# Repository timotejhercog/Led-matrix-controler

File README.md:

🚀 Led matrix controler

This project is currently under active development. More features, files, and updates are on the way!

📖 About The Project

Welcome to the repository! This project is still early in development, things are constantly changing, improving, and expanding.

✨ What's Here So Far

PCB files

MIDEM paper

📫 Stay Tuned

Thank you for checking out the project! Feel free to star ⭐ the repository to follow along with future updates.

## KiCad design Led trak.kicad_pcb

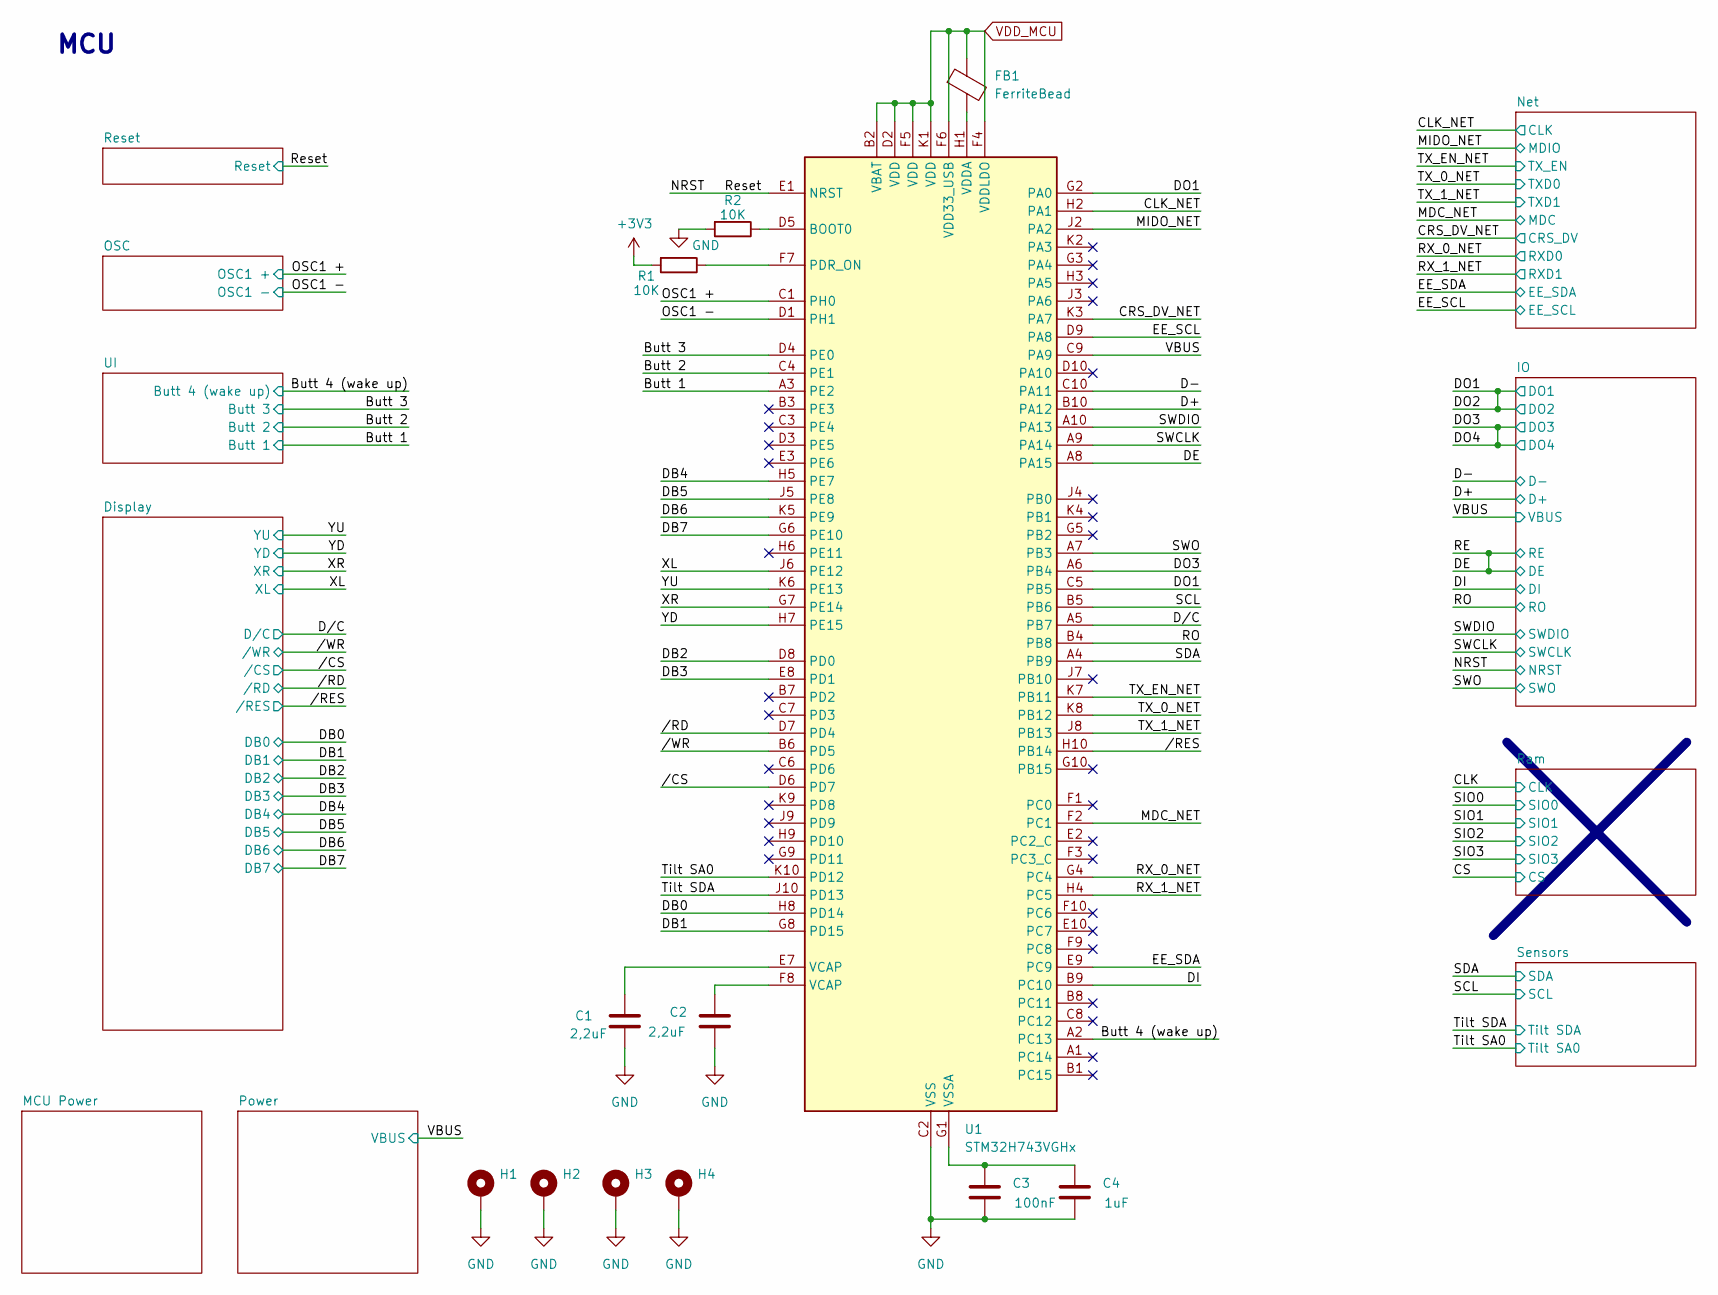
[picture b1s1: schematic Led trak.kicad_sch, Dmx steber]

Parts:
C1, C2: 2,2uF; C_0603_1608Metric
C3: 100nF; C_0603_1608Metric
C4: 1uF; C_0603_1608Metric
FB1: FerriteBead; C_0201_0603Metric
H1, H2, H3, H4: MountingHole_Pad_MP; MountingHole_3.2mm_M3_Pad_Via
R1, R2: 10K; C_0402_1005Metric
U1: STM32H743VGHx; TFBGA-100_8x8mm_Layout10x10_P0.8mm

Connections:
/Butt 1: U1.A3 (PE2); also elsewhere on the board
/Butt 2: U1.C4 (PE1); also elsewhere on the board
/Butt 3: U1.D4 (PE0); also elsewhere on the board
/Butt 4 (wake up): U1.A2 (PC13); also elsewhere on the board
/CLK_NET: U1.H2 (PA1); also elsewhere on the board
/CRS_DV_NET: U1.K3 (PA7); also elsewhere on the board
/D+: U1.B10 (PA12); also elsewhere on the board
/D-: U1.C10 (PA11); also elsewhere on the board
/DB0: U1.H8 (PD14); also elsewhere on the board
/DB1: U1.G8 (PD15); also elsewhere on the board
/DB2: U1.D8 (PD0); also elsewhere on the board
/DB3: U1.E8 (PD1); also elsewhere on the board
/DB4: U1.H5 (PE7); also elsewhere on the board
/DB5: U1.J5 (PE8); also elsewhere on the board
/DB6: U1.K5 (PE9); also elsewhere on the board
/DB7: U1.G6 (PE10); also elsewhere on the board
/DE: U1.A8 (PA15); also elsewhere on the board
/DI: U1.B9 (PC10); also elsewhere on the board
/DO1: U1.C5 (PB5), U1.G2 (PA0); also elsewhere on the board
/DO3: U1.A6 (PB4); also elsewhere on the board
/D/C: U1.A5 (PB7); also elsewhere on the board
/EE_SCL: U1.D9 (PA8); also elsewhere on the board
/EE_SDA: U1.E9 (PC9); also elsewhere on the board
/MDC_NET: U1.F2 (PC1); also elsewhere on the board
/MIDO_NET: U1.J2 (PA2); also elsewhere on the board
/NRST: U1.E1 (NRST); also elsewhere on the board
/OSC1 +: U1.C1 (PH0); also elsewhere on the board
/OSC1 -: U1.D1 (PH1); also elsewhere on the board
/RO: U1.B4 (PB8); also elsewhere on the board
/RX_0_NET: U1.G4 (PC4); also elsewhere on the board
/RX_1_NET: U1.H4 (PC5); also elsewhere on the board
/SCL: U1.B5 (PB6); also elsewhere on the board
/SDA: U1.A4 (PB9); also elsewhere on the board
/SWCLK: U1.A9 (PA14); also elsewhere on the board
/SWDIO: U1.A10 (PA13); also elsewhere on the board
/SWO: U1.A7 (PB3); also elsewhere on the board
/TX_0_NET: U1.K8 (PB12); also elsewhere on the board
/TX_1_NET: U1.J8 (PB13); also elsewhere on the board
/TX_EN_NET: U1.K7 (PB11); also elsewhere on the board
/Tilt SA0: U1.K10 (PD12); also elsewhere on the board
/Tilt SDA: U1.J10 (PD13); also elsewhere on the board
/VBUS: U1.C9 (PA9); also elsewhere on the board
/XL: U1.J6 (PE12); also elsewhere on the board
/XR: U1.G7 (PE14); also elsewhere on the board
/YD: U1.H7 (PE15); also elsewhere on the board
/YU: U1.K6 (PE13); also elsewhere on the board
//CS: U1.D6 (PD7); also elsewhere on the board
//RD: U1.D7 (PD4); also elsewhere on the board
//RES: U1.H10 (PB14); also elsewhere on the board
//WR: U1.B6 (PD5); also elsewhere on the board
GND: C1.2, C2.2, C3.2, C4.2, H1.MP, H2.MP, H3.MP, H4.MP, R2.2, U1.C2 (VSS), U1.E4 (VSS), U1.E5 (VSS), U1.E6 (VSS), U1.J1 (VSS); also elsewhere on the board
unnamed: C1.1, U1.E7 (VCAP)
unnamed: C2.1, U1.F8 (VCAP)
unnamed: R2.1, U1.D5 (BOOT0)
unnamed: R1.1, U1.F7 (PDR_ON)
unnamed: FB1.2, U1.H1 (VDDA)
unnamed: C3.1, C4.1, U1.G1 (VSSA)
VDD_MCU: FB1.1, R1.2, U1.B2 (VBAT), U1.D2 (VDD), U1.F4 (VDDLDO), U1.F5 (VDD), U1.F6 (VDD33_USB), U1.K1 (VDD); also elsewhere on the board

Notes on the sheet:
MCU

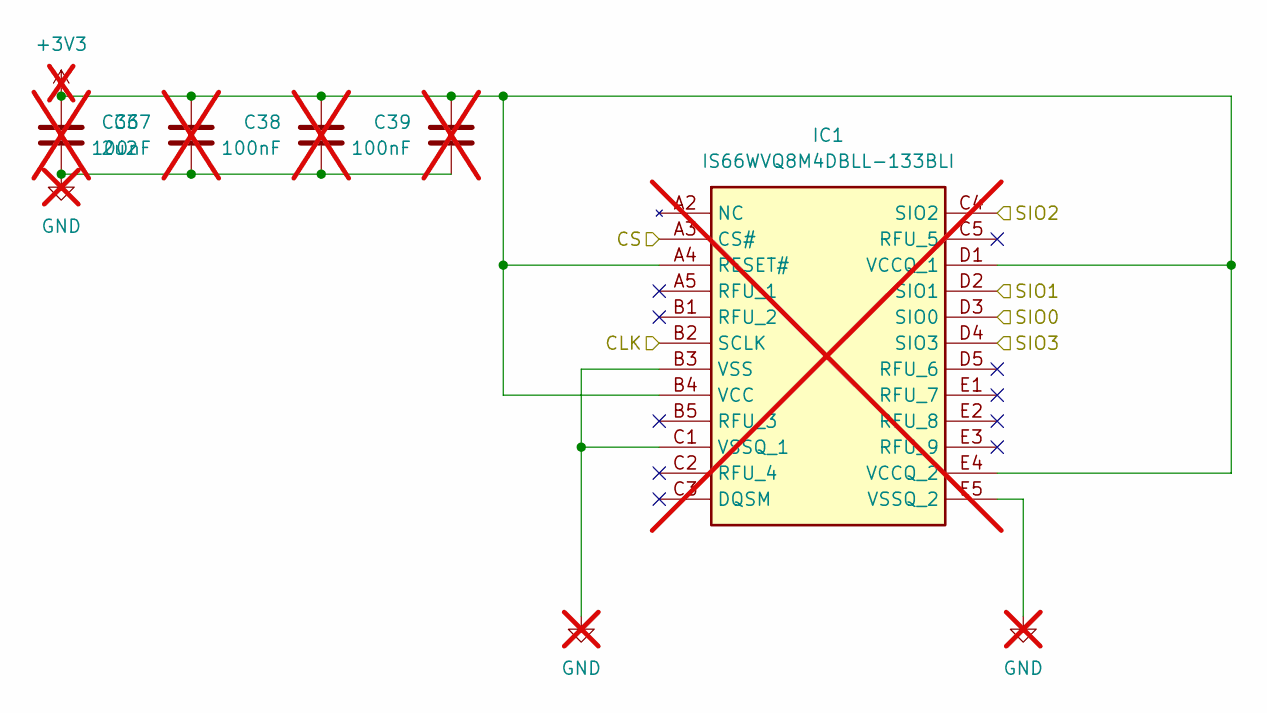
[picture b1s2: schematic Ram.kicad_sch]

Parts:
C36: 2u2; C_0603_1608Metric; not fitted
C37, C38, C39: 100nF; C_0402_1005Metric; not fitted
IC1: IS66WVQ8M4DBLL-133BLI; BGA24C100P5X5_600X800X120; Manufacturer_Part_Number IS66WVQ8M4DBLL-133BLI; Mouser Part Number 870-ISQ8M4DBLL133BLI; not fitted

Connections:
unnamed: C36.1, C37.1, C38.1, C39.1, IC1.A4 (RESET#), IC1.B4 (VCC), IC1.D1 (VCCQ_1), IC1.E4 (VCCQ_2)
unnamed: C36.2, C37.2, C38.2, C39.2, IC1.B3 (VSS), IC1.C1 (VSSQ_1), IC1.E5 (VSSQ_2)

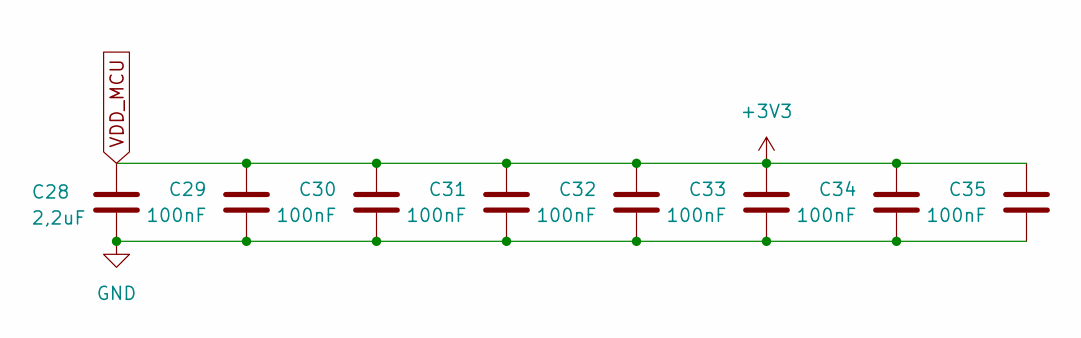
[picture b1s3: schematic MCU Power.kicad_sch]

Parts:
C28: 2,2uF; C_0603_1608Metric
C29, C30, C31, C32, C33, C34, C35: 100nF; C_0402_1005Metric

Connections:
GND: C28.2, C29.2, C30.2, C31.2, C32.2, C33.2, C34.2, C35.2; also elsewhere on the board
VDD_MCU: C28.1, C29.1, C30.1, C31.1, C32.1, C33.1, C34.1, C35.1; also elsewhere on the board

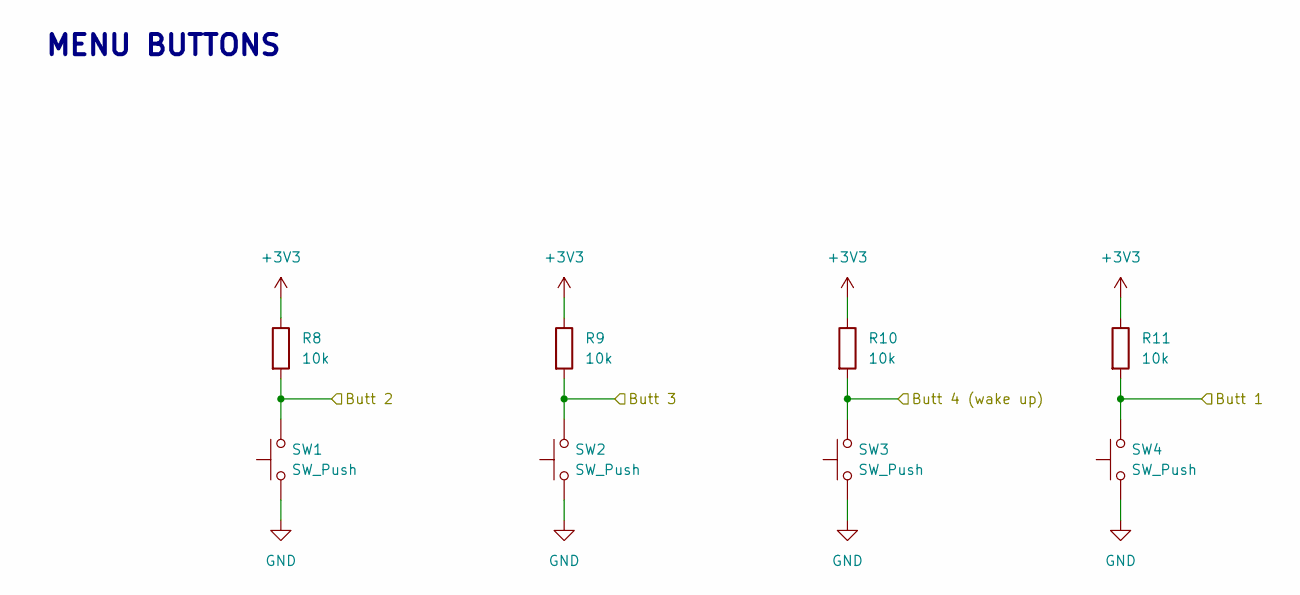
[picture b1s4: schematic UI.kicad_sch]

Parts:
R8, R9, R10, R11: 10k; C_0402_1005Metric
SW1, SW2, SW3, SW4: SW_Push; SW_Push_1TS009xxxx-xxxx-xxxx_6x6x5mm

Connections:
/Butt 1: R11.2, SW4.2; also elsewhere on the board
/Butt 2: R8.2, SW1.2; also elsewhere on the board
/Butt 3: R9.2, SW2.2; also elsewhere on the board
/Butt 4 (wake up): R10.2, SW3.2; also elsewhere on the board
GND: SW1.1, SW2.1, SW3.1, SW4.1; also elsewhere on the board
VDD_MCU: R8.1, R9.1, R10.1, R11.1; also elsewhere on the board

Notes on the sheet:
MENU BUTTONS

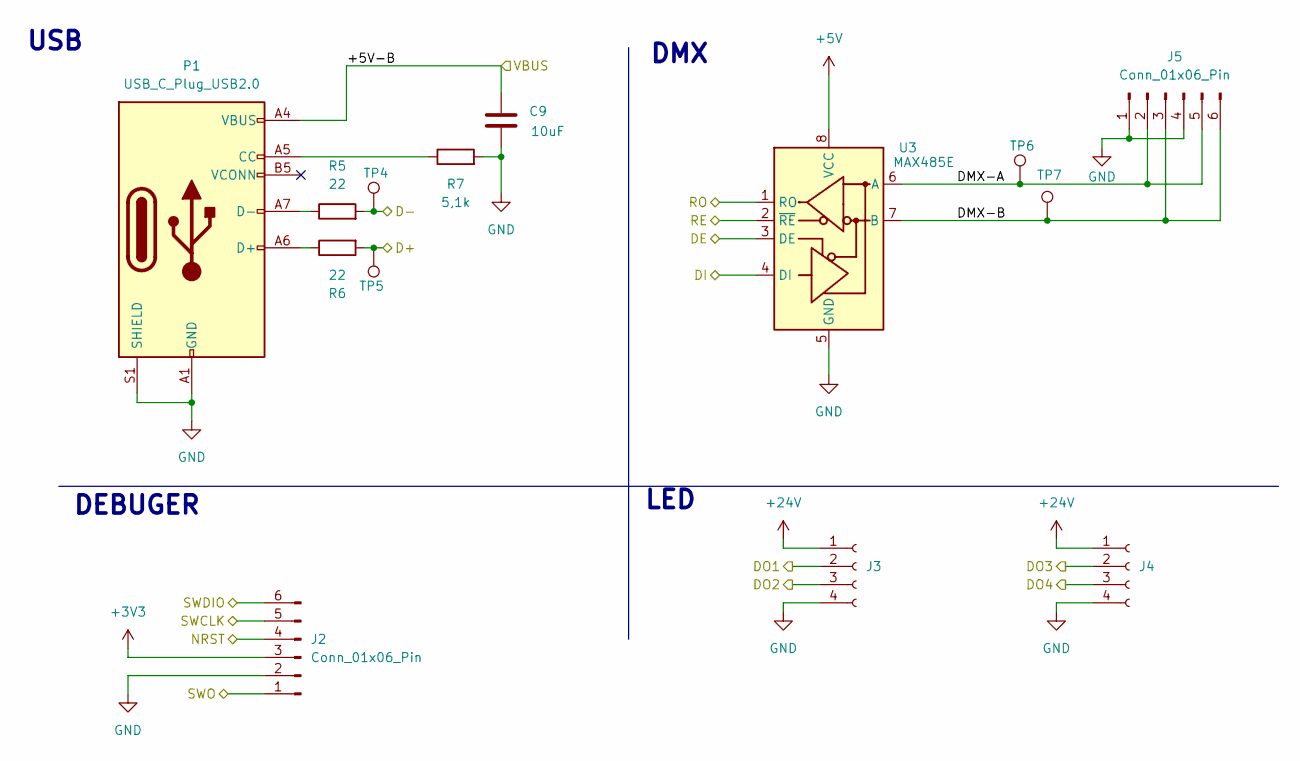
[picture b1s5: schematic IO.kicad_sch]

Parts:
C9: 10uF; C_0603_1608Metric
J2: Conn_01x06_Pin; PinSocket_1x06_P2.54mm_Vertical
J3, J4: Conn_01x04_Socket; Molex_PicoBlade_53047-0410_1x04_P1.25mm_Vertical
J5: Conn_01x06_Pin; Molex_PicoBlade_53047-0610_1x06_P1.25mm_Vertical
P1: USB_C_Plug_USB2.0; USB_C_Receptacle_HRO_TYPE-C-31-M-12
R5, R6: 22; C_0402_1005Metric
R7: 5,1k; C_0402_1005Metric
TP4, TP5, TP6, TP7: TestPoint; TestPoint_Pad_D1.5mm
U3: MAX485E; SOIC-8_3.9x4.9mm_P1.27mm

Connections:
+5V: U3.8 (VCC); also elsewhere on the board
+24V: J3.1, J4.1; also elsewhere on the board
/D+: R6.2, TP5.1; also elsewhere on the board
/D-: R5.2, TP4.1; also elsewhere on the board
/DE: U3.2 (~RE), U3.3 (DE); also elsewhere on the board
/DI: U3.4 (DI); also elsewhere on the board
/DO1: J3.2, J3.3; also elsewhere on the board
/DO3: J4.2, J4.3; also elsewhere on the board
/IO/DMX-A: J5.2, J5.5, TP6.1, U3.6 (A)
/IO/DMX-B: J5.3, J5.6, TP7.1, U3.7 (B)
/NRST: J2.4; also elsewhere on the board
/RO: U3.1 (RO); also elsewhere on the board
/SWCLK: J2.5; also elsewhere on the board
/SWDIO: J2.6; also elsewhere on the board
/SWO: J2.1; also elsewhere on the board
/VBUS: C9.1, P1.A4 (VBUS), P1.A9 (VBUS), P1.B4 (VBUS), P1.B9 (VBUS); also elsewhere on the board
GND: C9.2, J2.2, J3.4, J4.4, J5.1, J5.4, P1.A1 (GND), P1.A12 (GND), P1.B1 (GND), P1.B12 (GND), P1.S1 (SHIELD), R7.2, U3.5 (GND); also elsewhere on the board
unnamed: P1.A5 (CC), R7.1
unnamed: P1.A6 (D+), R6.1
unnamed: P1.A7 (D-), R5.1
VDD_MCU: J2.3; also elsewhere on the board

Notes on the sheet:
LED
DEBUGER
DMX
USB

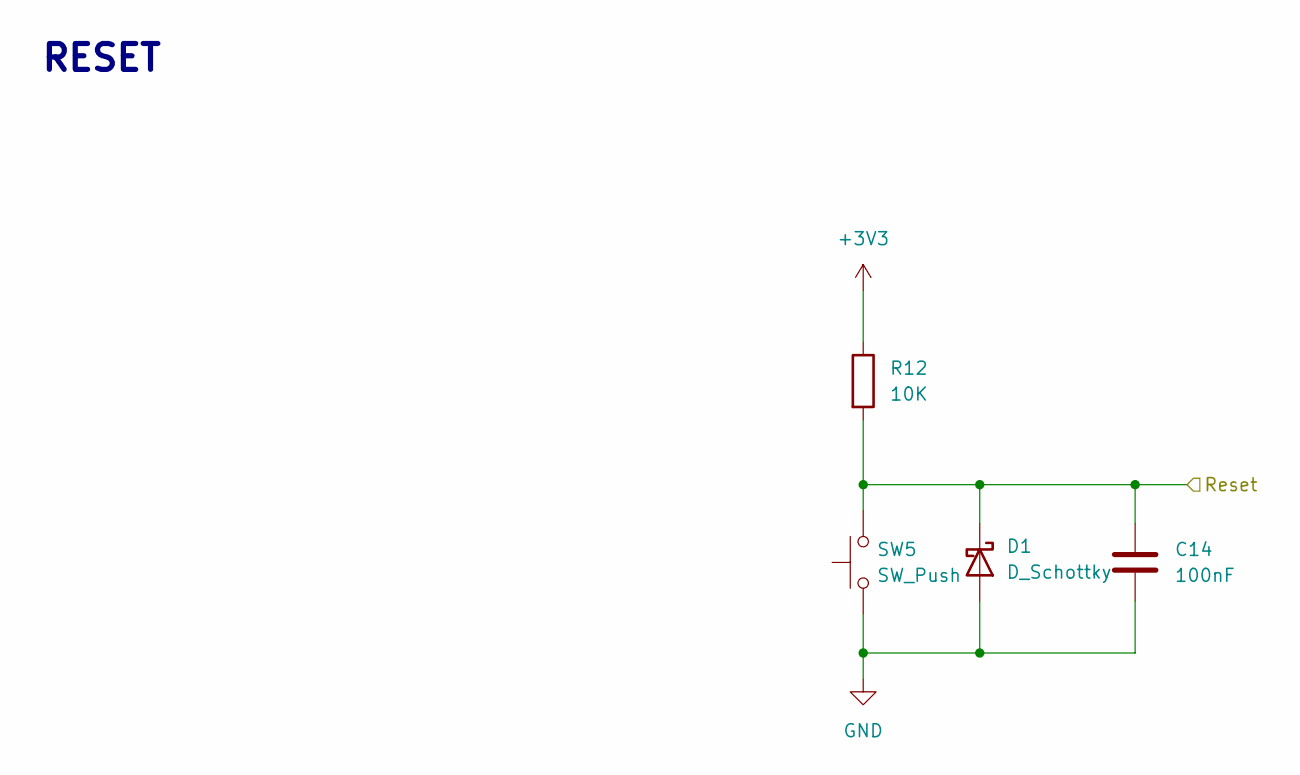
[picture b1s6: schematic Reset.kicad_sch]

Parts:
C14: 100nF; C_0402_1005Metric
D1: D_Schottky; D_SMA
R12: 10K; C_0402_1005Metric
SW5: SW_Push; SW_Push_1TS009xxxx-xxxx-xxxx_6x6x5mm

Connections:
/NRST: C14.1, D1.1 (K), R12.2, SW5.2; also elsewhere on the board
GND: C14.2, D1.2 (A), SW5.1; also elsewhere on the board
VDD_MCU: R12.1; also elsewhere on the board

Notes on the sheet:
RESET

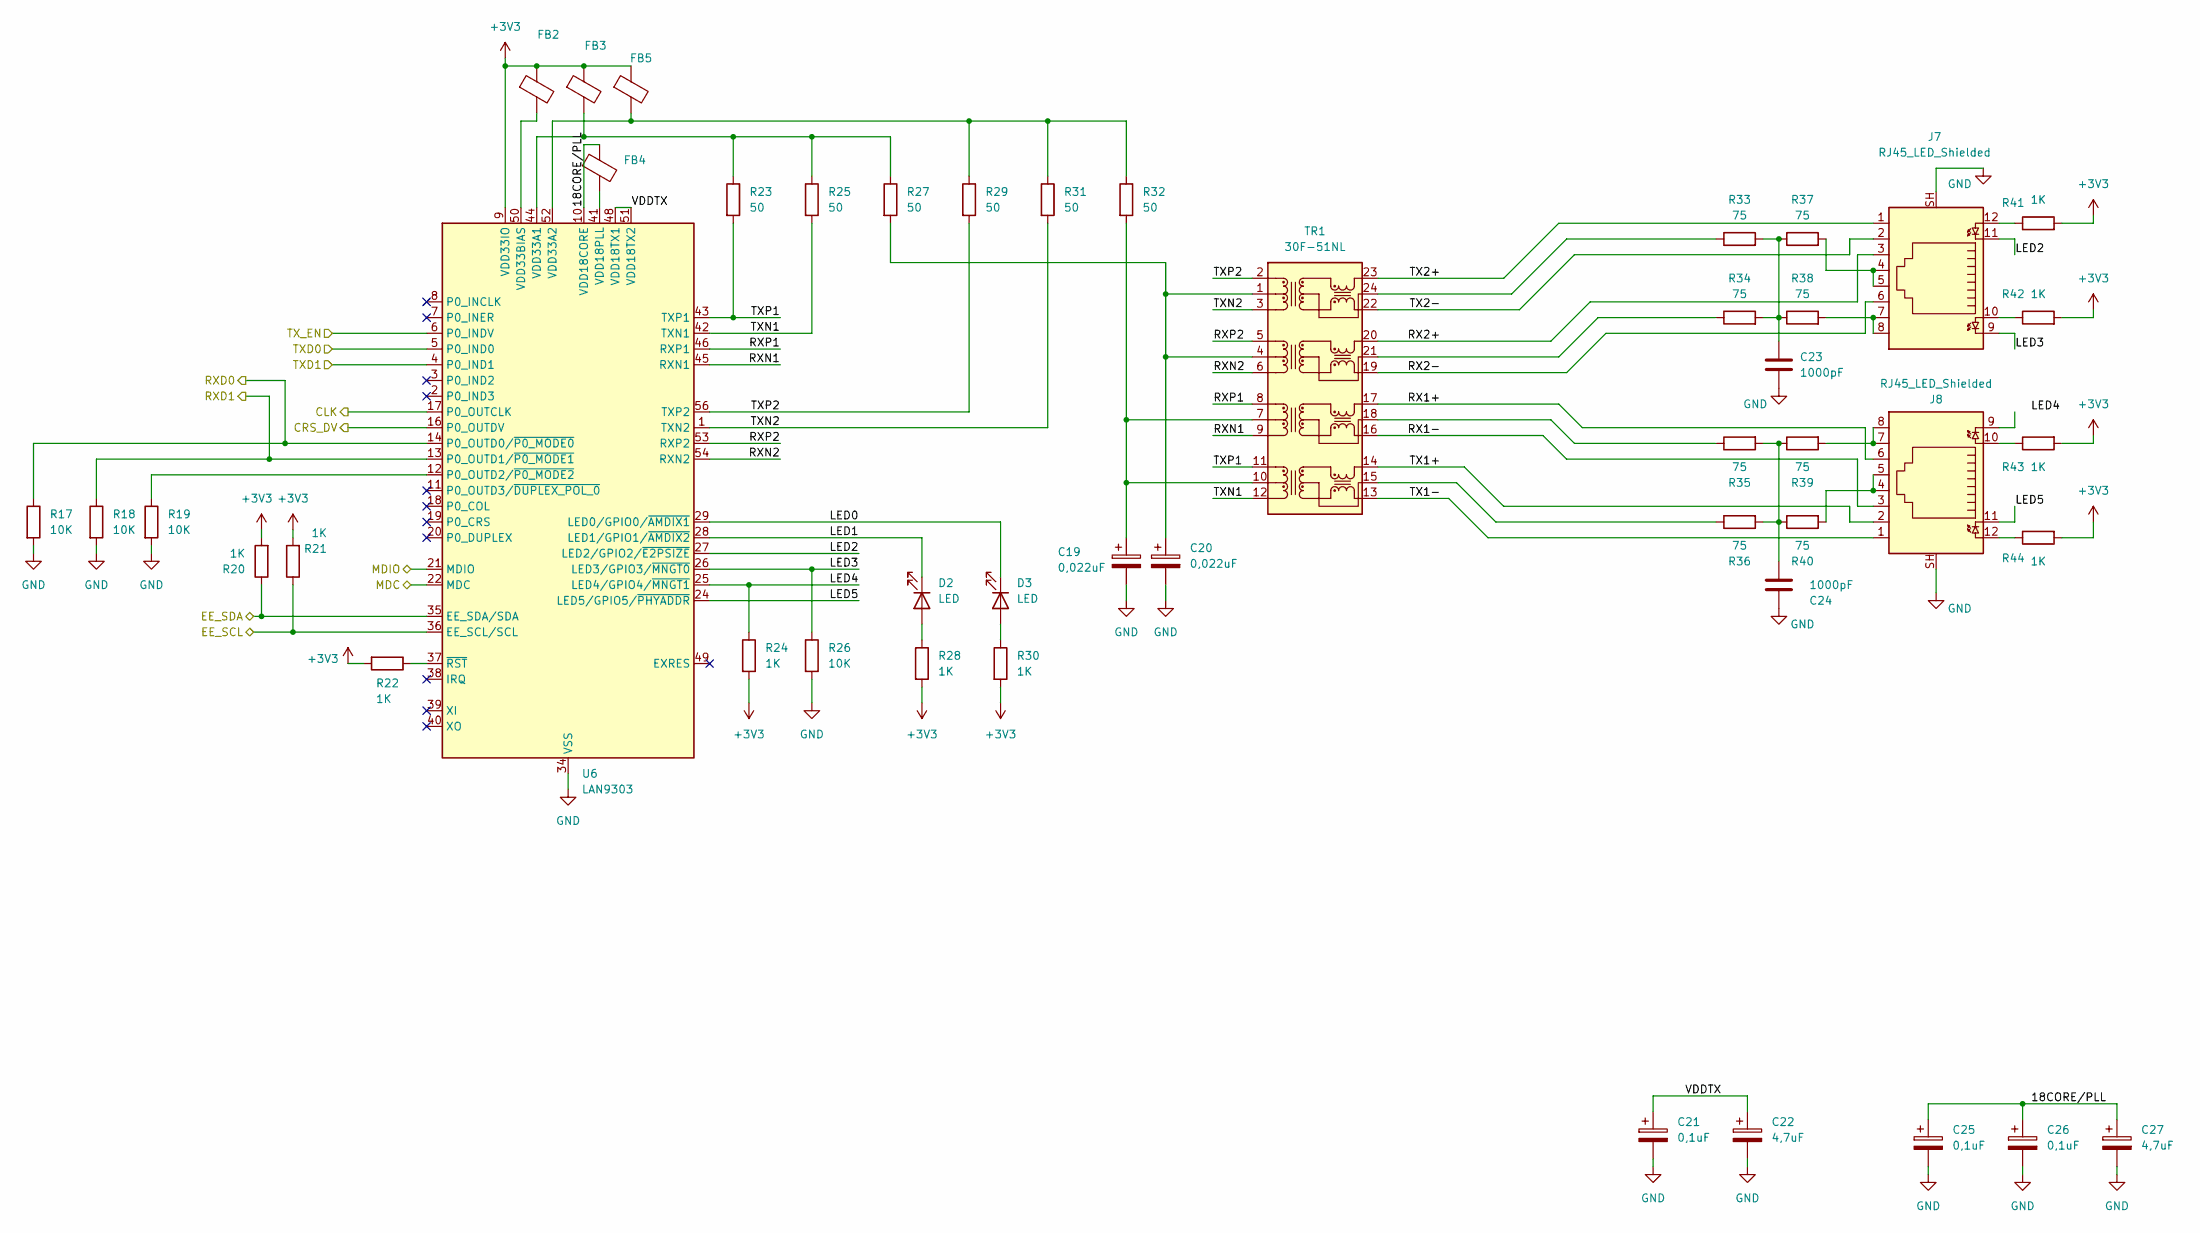
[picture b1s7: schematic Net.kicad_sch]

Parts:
C19, C20: 0,022uF; CP_Elec_4x5.4
C21, C25, C26: 0,1uF; C_0402_1005Metric
C22, C27: 4,7uF; C_0402_1005Metric
C23, C24: 1000pF; C_0402_1005Metric
D2, D3: LED; LED_0603_1608Metric
FB2, FB3, FB4, FB5: FerriteBead; C_0201_0603Metric
J7, J8: RJ45_LED_Shielded; RJ45_Amphenol_RJHSE538X
R17, R18, R19, R26: 10K; C_0402_1005Metric
R20, R21, R22, R24, R28, R30, R41, R42, R43, R44: 1K; C_0402_1005Metric
R23, R25, R27, R29, R31, R32: 50; C_0402_1005Metric
R33, R34, R35, R36, R37, R38, R39, R40: 75; C_0402_1005Metric
TR1: 30F-51NL; Transformer_Ethernet_YDS_30F-51NL_SO-24_7.1x15.1mm
U6: LAN9303; QFN-56-1EP_8x8mm_P0.5mm_EP5.9x5.9mm_ThermalVias

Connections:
/CLK_NET: U6.17 (P0_OUTCLK); also elsewhere on the board
/CRS_DV_NET: U6.16 (P0_OUTDV); also elsewhere on the board
/EE_SCL: R21.1, U6.36 (EE_SCL/SCL); also elsewhere on the board
/EE_SDA: R20.1, U6.35 (EE_SDA/SDA); also elsewhere on the board
/MDC_NET: U6.22 (MDC); also elsewhere on the board
/MIDO_NET: U6.21 (MDIO); also elsewhere on the board
/Net/18CORE/PLL: C25.1, C26.1, C27.1, FB4.1, U6.10 (VDD18CORE), U6.31 (VDD18CORE)
/Net/LED0: D3.1 (K), U6.29 (LED0/GPIO0/~AMDIX1)
/Net/LED1: D2.1 (K), U6.28 (LED1/GPIO1/~AMDIX2)
/Net/LED2: J7.11, U6.27 (LED2/GPIO2/~E2PSIZE)
/Net/LED3: J7.9, R26.1, U6.26 (LED3/GPIO3/~MNGT0)
/Net/LED4: R24.1, U6.25 (LED4/GPIO4/~MNGT1)
/Net/LED5: J8.11, U6.24 (LED5/GPIO5/~PHYADDR)
/Net/RX1+: J8.6, TR1.17 (MX3+)
/Net/RX1-: J8.3, TR1.16 (MX3-)
/Net/RX2+: J7.3, TR1.20 (MX2+)
/Net/RX2-: J7.6, TR1.19 (MX2-)
/Net/RXN1: TR1.9 (TD3-), U6.45 (RXN1)
/Net/RXN2: TR1.6 (TD2-), U6.54 (RXN2)
/Net/RXP1: TR1.8 (TD3+), U6.46 (RXP1)
/Net/RXP2: TR1.5 (TD2+), U6.53 (RXP2)
/Net/TX1+: J8.2, TR1.14 (MX4+)
/Net/TX1-: J8.1, TR1.13 (MX4-)
/Net/TX2+: J7.1, TR1.23 (MX1+)
/Net/TX2-: J7.2, TR1.22 (MX1-)
/Net/TXN1: R25.2, TR1.12 (TD4-), U6.42 (TXN1)
/Net/TXN2: R31.2, TR1.3 (TD1-), U6.1 (TXN2)
/Net/TXP1: R23.2, TR1.11 (TD4+), U6.43 (TXP1)
/Net/TXP2: R29.2, TR1.2 (TD1+), U6.56 (TXP2)
/Net/VDDTX: C21.1, C22.1, U6.48 (VDD18TX1), U6.51 (VDD18TX2)
/RX_0_NET: R17.1, U6.14 (P0_OUTD0/~P0_MODE0); also elsewhere on the board
/RX_1_NET: R18.1, U6.13 (P0_OUTD1/~P0_MODE1); also elsewhere on the board
/TX_0_NET: U6.5 (P0_IND0); also elsewhere on the board
/TX_1_NET: U6.4 (P0_IND1); also elsewhere on the board
/TX_EN_NET: U6.6 (P0_INDV); also elsewhere on the board
GND: C19.2, C20.2, C21.2, C22.2, C23.2, C24.1, C25.2, C26.2, C27.2, J7.SH, J8.SH, R17.2, R18.2, R19.2, R26.2, U6.34 (VSS), U6.57 (VSS); also elsewhere on the board
unnamed: C19.1, R32.2, TR1.7 (CT), TR1.10 (CT)
unnamed: C20.1, R27.2, TR1.1 (CT), TR1.4 (CT)
unnamed: C23.1, R33.2, R34.2, R37.1, R38.1
unnamed: C24.2, R35.2, R36.2, R39.1, R40.1
unnamed: D2.2 (A), R28.1
unnamed: D3.2 (A), R30.1
unnamed: FB3.2, R23.1, R25.1, R27.1, U6.44 (VDD33A1), U6.47 (VDD33A1)
unnamed: FB5.2, R29.1, R31.1, R32.1, U6.52 (VDD33A2), U6.55 (VDD33A2)
unnamed: J7.4, J7.5, R37.2
unnamed: J7.7, J7.8, R38.2
unnamed: J7.10, R42.1
unnamed: J7.12, R41.1
unnamed: J8.4, J8.5, R40.2
unnamed: J8.7, J8.8, R39.2
unnamed: J8.10, R43.1
unnamed: J8.12, R44.1
unnamed: R33.1, TR1.24 (CT)
unnamed: R34.1, TR1.21 (CT)
unnamed: R35.1, TR1.18 (CT)
unnamed: R36.1, TR1.15 (CT)
unnamed: R19.1, U6.12 (P0_OUTD2/~P0_MODE2)
unnamed: FB4.2, U6.41 (VDD18PLL)
unnamed: FB2.2, U6.50 (VDD33BIAS)
unnamed: R22.1, U6.37 (~RST)
VDD_MCU: FB2.1, FB3.1, FB5.1, R20.2, R21.2, R22.2, R24.2, R28.2, R30.2, R41.2, R42.2, R43.2, R44.2, U6.9 (VDD33IO), U6.15 (VDD33IO), U6.23 (VDD33IO), U6.30 (VDD33IO), U6.32 (VDD33IO), U6.33 (VDD33IO); also elsewhere on the board

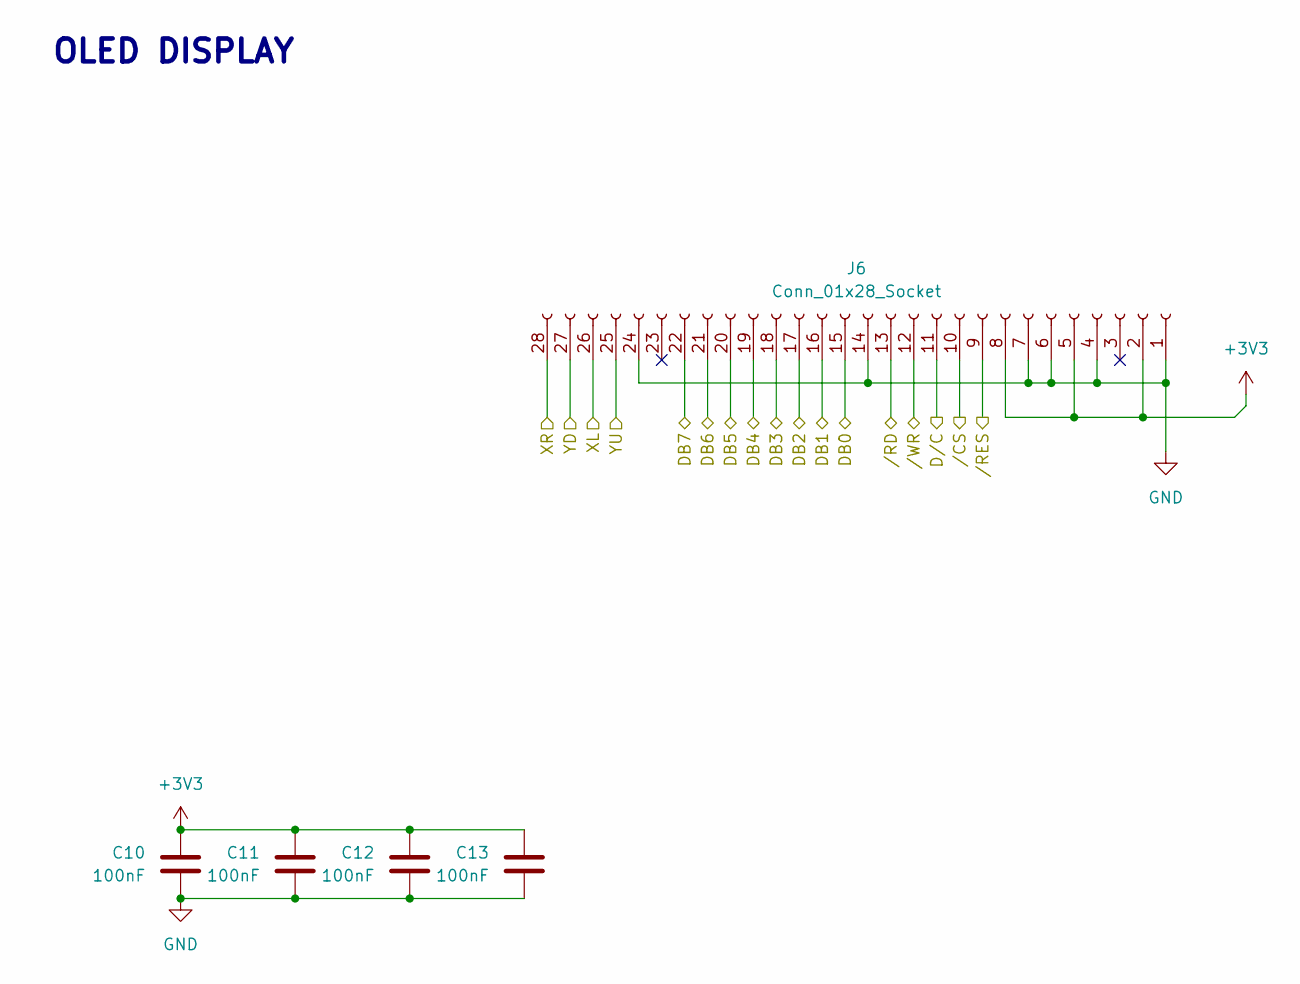
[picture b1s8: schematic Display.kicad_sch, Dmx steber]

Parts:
C10: 100nF; C_0603_1608Metric
C11, C12, C13: 100nF; C_0402_1005Metric
J6: Conn_01x28_Socket; 5051102891

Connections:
/DB0: J6.15; also elsewhere on the board
/DB1: J6.16; also elsewhere on the board
/DB2: J6.17; also elsewhere on the board
/DB3: J6.18; also elsewhere on the board
/DB4: J6.19; also elsewhere on the board
/DB5: J6.20; also elsewhere on the board
/DB6: J6.21; also elsewhere on the board
/DB7: J6.22; also elsewhere on the board
/D/C: J6.11; also elsewhere on the board
/XL: J6.26; also elsewhere on the board
/XR: J6.28; also elsewhere on the board
/YD: J6.27; also elsewhere on the board
/YU: J6.25; also elsewhere on the board
//CS: J6.10; also elsewhere on the board
//RD: J6.13; also elsewhere on the board
//RES: J6.9; also elsewhere on the board
//WR: J6.12; also elsewhere on the board
GND: C10.2, C11.2, C12.2, C13.2, J6.1, J6.4, J6.6, J6.7, J6.14, J6.24; also elsewhere on the board
VDD_MCU: C10.1, C11.1, C12.1, C13.1, J6.2, J6.5, J6.8; also elsewhere on the board

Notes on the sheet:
OLED DISPLAY

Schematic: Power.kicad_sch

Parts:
C5, C6: 4,7uF; C_0603_1608Metric
C7, C8: 15uF; C_0603_1608Metric
J1: Screw_Terminal_01x02; Molex_Micro-Latch_53253-0270_1x02_P2.00mm_Vertical
L1, L2: 2,2uH; L_1812_4532Metric
Q1, Q2: LMR60420
R3, R4: 16,5; C_0402_1005Metric
TP1, TP2, TP3: TestPoint; TestPoint_Pad_D1.5mm
U2: TPS2116DRL; SOT-583-8

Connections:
+5V: C5.2, Q1.1 (VIN), Q1.9 (EN), U2.2 (VOUT), U2.5 (MODE), U2.7 (VOUT); also elsewhere on the board
+24V: C6.2, J1.2, Q2.1 (VIN), Q2.9 (EN), TP1.1; also elsewhere on the board
/Power/+5V-A: L2.2, Q2.6 (FB), TP3.1, U2.3 (VIN1), U2.4 (PR1)
/VBUS: U2.6 (VIN2); also elsewhere on the board
GND: C5.1, C6.1, J1.1, Q1.2 (PGND), Q1.7 (MODE/SYNC), Q2.2 (PGND), Q2.7 (MODE/SYNC), R3.2, R4.2, U2.1 (GND); also elsewhere on the board
unnamed: C7.1, Q1.4 (BOOT)
unnamed: Q1.8 (RT), R3.1
unnamed: C7.2, L1.1, Q1.3 (SW)
unnamed: C8.1, Q2.4 (BOOT)
unnamed: Q2.8 (RT), R4.1
unnamed: C8.2, L2.1, Q2.3 (SW)
VDD_MCU: L1.2, Q1.6 (FB), TP2.1; also elsewhere on the board

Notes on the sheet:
+3V3
+5V
POWER IN

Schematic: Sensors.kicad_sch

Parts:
C15: 10uF; C_0402_1005Metric
C16: 100nF; C_0402_1005Metric
R13, R14, R15, R16: 10k; C_0402_1005Metric
U4: LIS3DH; LGA-16_3x3mm_P0.5mm_LayoutBorder3x5y
U5: HDC1080; Texas_PWSON-N6

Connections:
/SCL: R15.2, U5.6 (SCL); also elsewhere on the board
/SDA: R16.2, U5.1 (SDA); also elsewhere on the board
/Tilt SA0: R13.2, U4.7 (SDO); also elsewhere on the board
/Tilt SDA: U4.6 (SDI); also elsewhere on the board
GND: C15.2, C16.2, U4.5 (GND), U4.9 (INT2), U4.10 (GND), U4.11 (INT1), U4.12 (GND), U5.2 (GND); also elsewhere on the board
unnamed: R14.2, U4.4 (SPC)
VDD_MCU: C15.1, C16.1, R13.1, R14.1, R15.1, R16.1, U4.1 (VDD_IO), U4.14 (VDD), U5.5 (VCC); also elsewhere on the board

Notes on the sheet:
GYRO
TMP

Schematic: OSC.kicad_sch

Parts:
C17, C18: 5,1pF; C_0402_1005Metric
Y1: 25MHz; Crystal_SMD_Abracon_ABM10-4Pin_2.5x2.0mm

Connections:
/OSC1 +: C17.1, Y1.2; also elsewhere on the board
/OSC1 -: C18.1, Y1.1; also elsewhere on the board
GND: C17.2, C18.2; also elsewhere on the board

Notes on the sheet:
OSCILATOR CRYSTAL

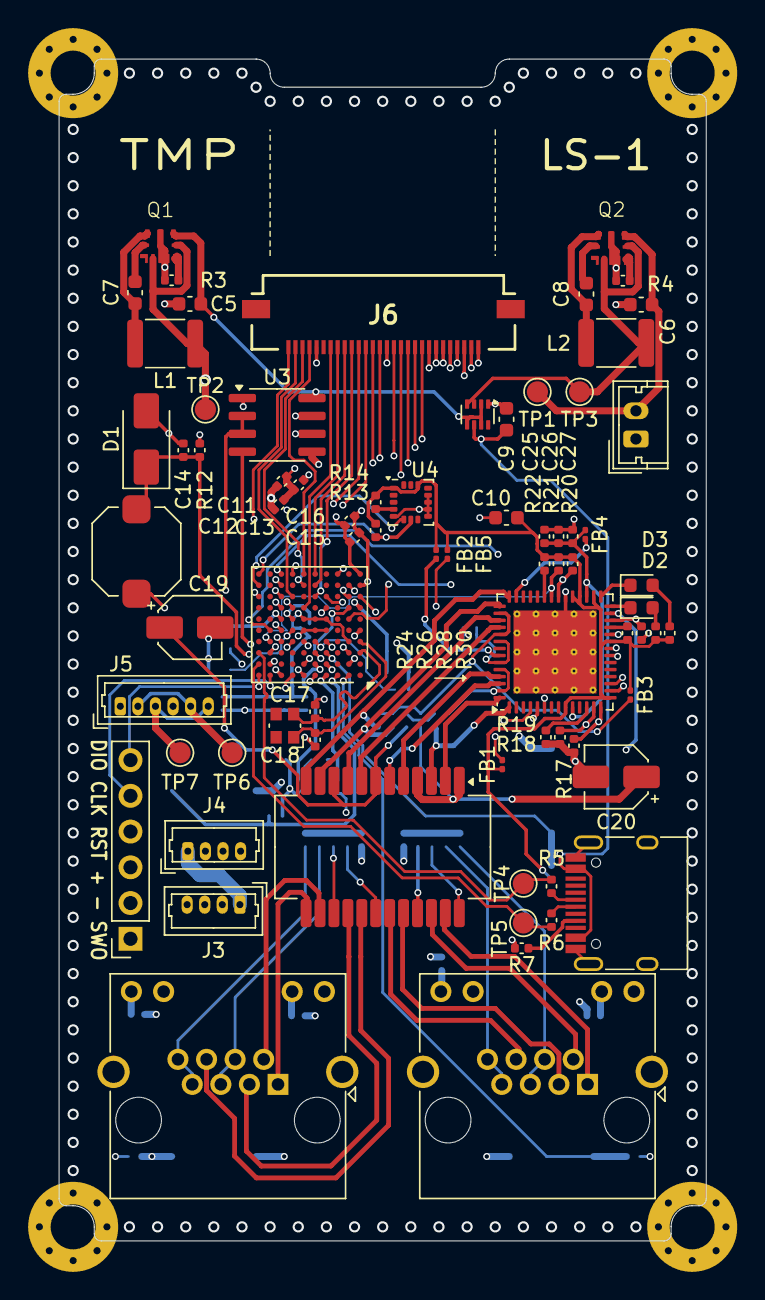
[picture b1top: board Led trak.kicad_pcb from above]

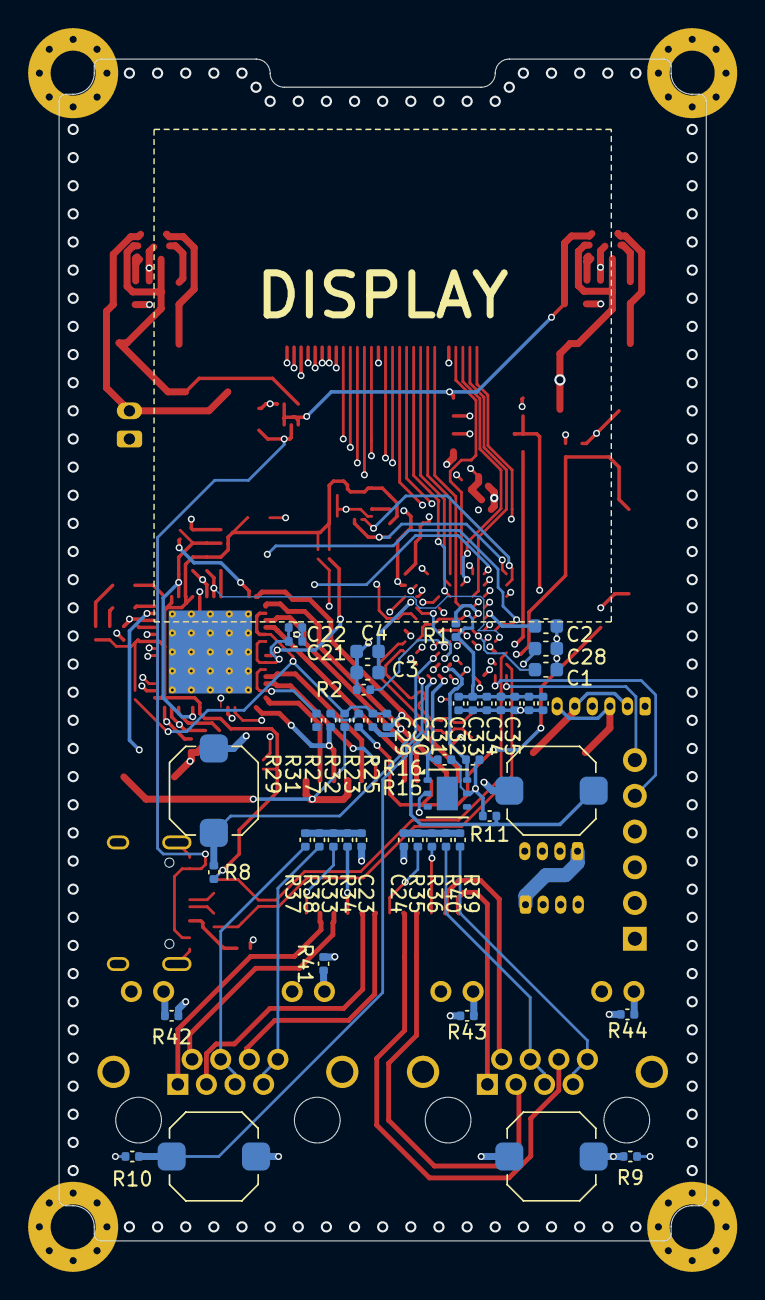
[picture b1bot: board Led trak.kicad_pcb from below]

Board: 6 copper layers, 46.0 x 84.0 mm, 124 parts (47 on the bottom side), 121 nets.
